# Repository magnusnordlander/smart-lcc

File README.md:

# Smart LCC

A smarter LCC for the Lelit Bianca V2, with Wi-Fi and stuff.

Based on the protocol dissection I'm doing in [magnusnordlander/lelit-bianca-protocol](https://github.com/magnusnordlander/lelit-bianca-protocol).

**This project is moving to [https://github.com/variegated-coffee](https://github.com/variegated-coffee). Don't manufacture this board, there's a new revision coming.**

## Status

Consider this project beta quality.

The revision B PCB works well. Manufacturing files are available in the `pcb/` directory. Unless you're *very* good at soldering fine pitch by hand, I suggest manufacturing with SMT assembly. I've used JLCPCB for my manufacturing runs, and the files have worked well there. I do have some spares of both the Rev A PCB (just the PCB) and the Rev B PCB (the difficult components already soldered, but does need a connector, buttons, a display and an Arduino). If you have experience of embedded programming, want to help with the project and you want one of the PCBs, reach out.

I am considering making a Rev C PCB that doesn't use an Arduino, but rather RP2040 and ESP32 chips directly. This would allow for a relocated display connector (similar to the original LCC) and a better antenna, which is useful since the board is located inside a metal enclosure. We'll have to see though.

Considering this plugs in to an expensive machine it bears to mention: Anything you do with this, you do at your own risk. Components have been fried already during the course of this project. Your machine uses both line voltage power, high pressured hot water, steam and other dangerous components. There is a risk of both damaging the machine, personal injury and property damage, the liability for which you assume yourself. This is not the stage to get on board with this project if you aren't willing to deal with those risks. 

### A note on Bianca versions

This project has only been tested on a Bianca V2. There are (at the time of writing) three versions of the Bianca, V1, V2, and V3. To my understanding it should work on a Bianca V1, but it's untested. As for the Bianca V3, it features upgraded hardware (a different solenoid valve with high/low flow signals), which this project doesn't support. Since I don't have access to a Bianca V3 (for reverse engineering or otherwise), support is currently not on the roadmap.

The LCC-relevant hardware differences between a V2 and a V3 Bianca (to my understanding) are the following:

* A new solenoid to control full/low flow from the pump (upgradable via the V3 upgrade kit)
* The power light now an LED and software controlled (not a part of the V3 upgrade kit)

Most notably, the Gicar box is the same, which is very interesting.

Like I said, I do not have access to a Bianca V3, so reverse engineering the protocol changes for the V3 would be difficult, and validation would be impossible. That being said, if someone were to reverse engineer the protocol changes, a new version of this firmware could be made that would be backwards-compatible with the Bianca V2. That is absolutely an interesting proposition.

## Project goals

Create a smart replacement for the "LCC" PID module used in the Lelit Bianca with open source hardware and software.

## Architecture

### Hardware
This project is using the Arduino RP2040 Connect, a dual core ARM Cortex-M0+ board with a Ublox Nina W102 module.

A custom PCB has been designed (see `pcb/`) that is designed to fit in the original LCC enclosure. A BOM for components is also available. Aside from the Arduino RP2040 Connect, the PCB has push buttons for + and -, a resistor divider for the 5V Control Board UART signal, and a flat flex connector for a SSD1309 based OLED. The PCB has been designed with surface mount components, but uses relatively large 1206 caps and resistors, which are somewhat simple to hand solder.

#### Possible future revision
I have been considering a new hardware revision, which instead of using an Arduino RP2040 Connect, uses just a plain RP2040, and a plain ESP32 (of some kind, though if I know myself, it'll probably be an ESP32-S3).

The main motivations are the following: 

* Allowing a better WiFi antenna (the Bianca is basically a faraday cage, so a better antenna would be beneficial)
* Allowing for separate programming ports on the board for the ESP32 and the RP2040
* Possibly attaching the RP2040 QSPI Flash to the ESP32 as well, for easier OTA updates
* Allowing for a cutout for the display ribbon cable, similar to the cutout on the original LCC board

There's also a couple of more errata like things I would add in a new revision:

* Use just a Zener instead of resistor divider to shift the 5V UART to 3V3

This being said, I haven't made up my mind about whether to do a future revision at all.

### Firmware (1.0.0, current)
The project is using arduino-cli, with earlephilhower/arduino-pico. Core 0 runs UI and external communications, and will communicate with core 1 through `pico_util/queue`. Core1 does not *store* it's parameters. Core0 reads them from LittleFS, and passes them to Core1 through regular message passing.

#### Usage
Hold the plus button while booting to trigger configuration mode. In configuration mode, a safe packet is continually sent to the control board, and a WiFi access point is created, with the SSID `LCC-XXXXXX`, where `XXXXXX` is the last 6 hex digits of the unit's MAC address. It is password protected, using the same password as the SSID, (i.e. `LCC-XXXXXX`). Therein you can configure your WiFi network and MQTT settings.

Hold the minus button while booting to trigger OTA mode. As in configuration mode, a safe packet is continually sent to the control board. It connects to the WiFi configured in configuration mode. Use ArduinoOTA to send new firmware. The controller doesn't automatically reboot after OTA, so after the OTA is complete and the display goes blank, manually cycle power.

#### RP2040 Core 0
* UI controller
* External communication

#### RP2040 Core 1
* System controller
  * Safety critical, uses the entire core for itself
  * Communicates with the Control Board
  * Performs a safety check, ensuring that temperatures in the boilers never exceed safe limits, and that both boilers are never running simultaneously.
  * Responsible for kicking the watchdog
    * Reboots if Core 0 isn't handling its messages (i.e. has crashed or is frozen)
  * Responsible for PID, keeping water in the boiler, running pumps etc.

#### Core communication protocol

##### Core1 to Core0

* One message type
  * Timestamp (absolute_time_t) 
  * Brew temperature
  * Brew set point
  * Brew PID settings
  * Brew PID parameters
  * Service temperature
  * Service set point
  * Service PID settings
  * Service PID parameters
  * Eco mode
  * System state
    * Idle
    * Heatup
    * Warm
    * Sleeping
    * Bailed
    * First run (fill all the boilers before heating them)
  * Bail reason
  * Brewing
  * Filling service boiler
  * Water low

##### Core0 to Core1

* Multiple message types
  * Set Brew Set Point (Non compensated)
  * Set Brew PID Parameters
  * Set Service Set Point
  * Set Service PID Parameters
  * Set Eco Mode (on/off)
  * Set Sleep mode (on/off)
  * Unbail
  * Trigger first run
* Payloads
  * Float 1
    * Brew set point
    * Service boiler set point
    * Kp
  * Float 2
    * Ki
  * Float 3
    * Kd
  * Bool
    * Eco mode
    * Sleep mode

### Firmware 1.1.0
In this firmware, Core0 and Core1 will swap functions.

### Firmware 2.0.0
In this firmware, a custom firmware for the Ublox Nina W102 will be developed to handle network communication.

### Reference material
(In no particular order)

* https://github.com/improv-wifi/sdk-cpp
* https://www.youtube.com/watch?v=fAEDHOUJCEo
* Random facts about the stock implementation:
  * Some implementation details are available in https://www.1st-line.com/wp-content/uploads/2018/12/Parameter-settings-technical-menu-Bianca-PL162T.pdf
    * Original parameters (not necessarily applicable since PID parameters are hightly implementation dependent):
      * Brew boiler
        * Kp: 0.8
        * Ki: 0.04
        * Kd: 12
        * On/off delta: 15°C
      * Service boiler
        * Kp: 20
        * Ki: 0
        * Kd: 20
        * On/off delta: 0
      * Brew boiler offset: 10°C
    * A "full" heatup cycle goes to 130°C first, then drops to set temperature
      * Triggered when the temperature on power on is less than 70°C
    * Service boiler is not PID controlled (even though it can be). Even if it *were*, having a Ki of 0, means it's a PD controller. It's a simple on/off controller.
  * Minimum on/off-time seems to be around 100-120 ms
  * When in eco mode, a warmup consists of running the coffee boiler full blast, holding the temperature around 130°C for 4 minutes, then dropping to the set point
  * When in regular mode, there is a kind of time slot system for which boiler is used. The time slots are 1 second wide.
  * Shot saving seems to be implemented by simply blocking new brews from starting when the tank is empty. There's no fanciness with allowing it to run for a certain amount of time or anything.
  * It takes about 3 seconds for the LCC to pick up on an empty water tank (presumably to debounce the signal)

## Licensing

The firmware is MIT licensed (excepting dependencies, which have their own, compatible licenses), and the hardware is CERN-OHL-P.

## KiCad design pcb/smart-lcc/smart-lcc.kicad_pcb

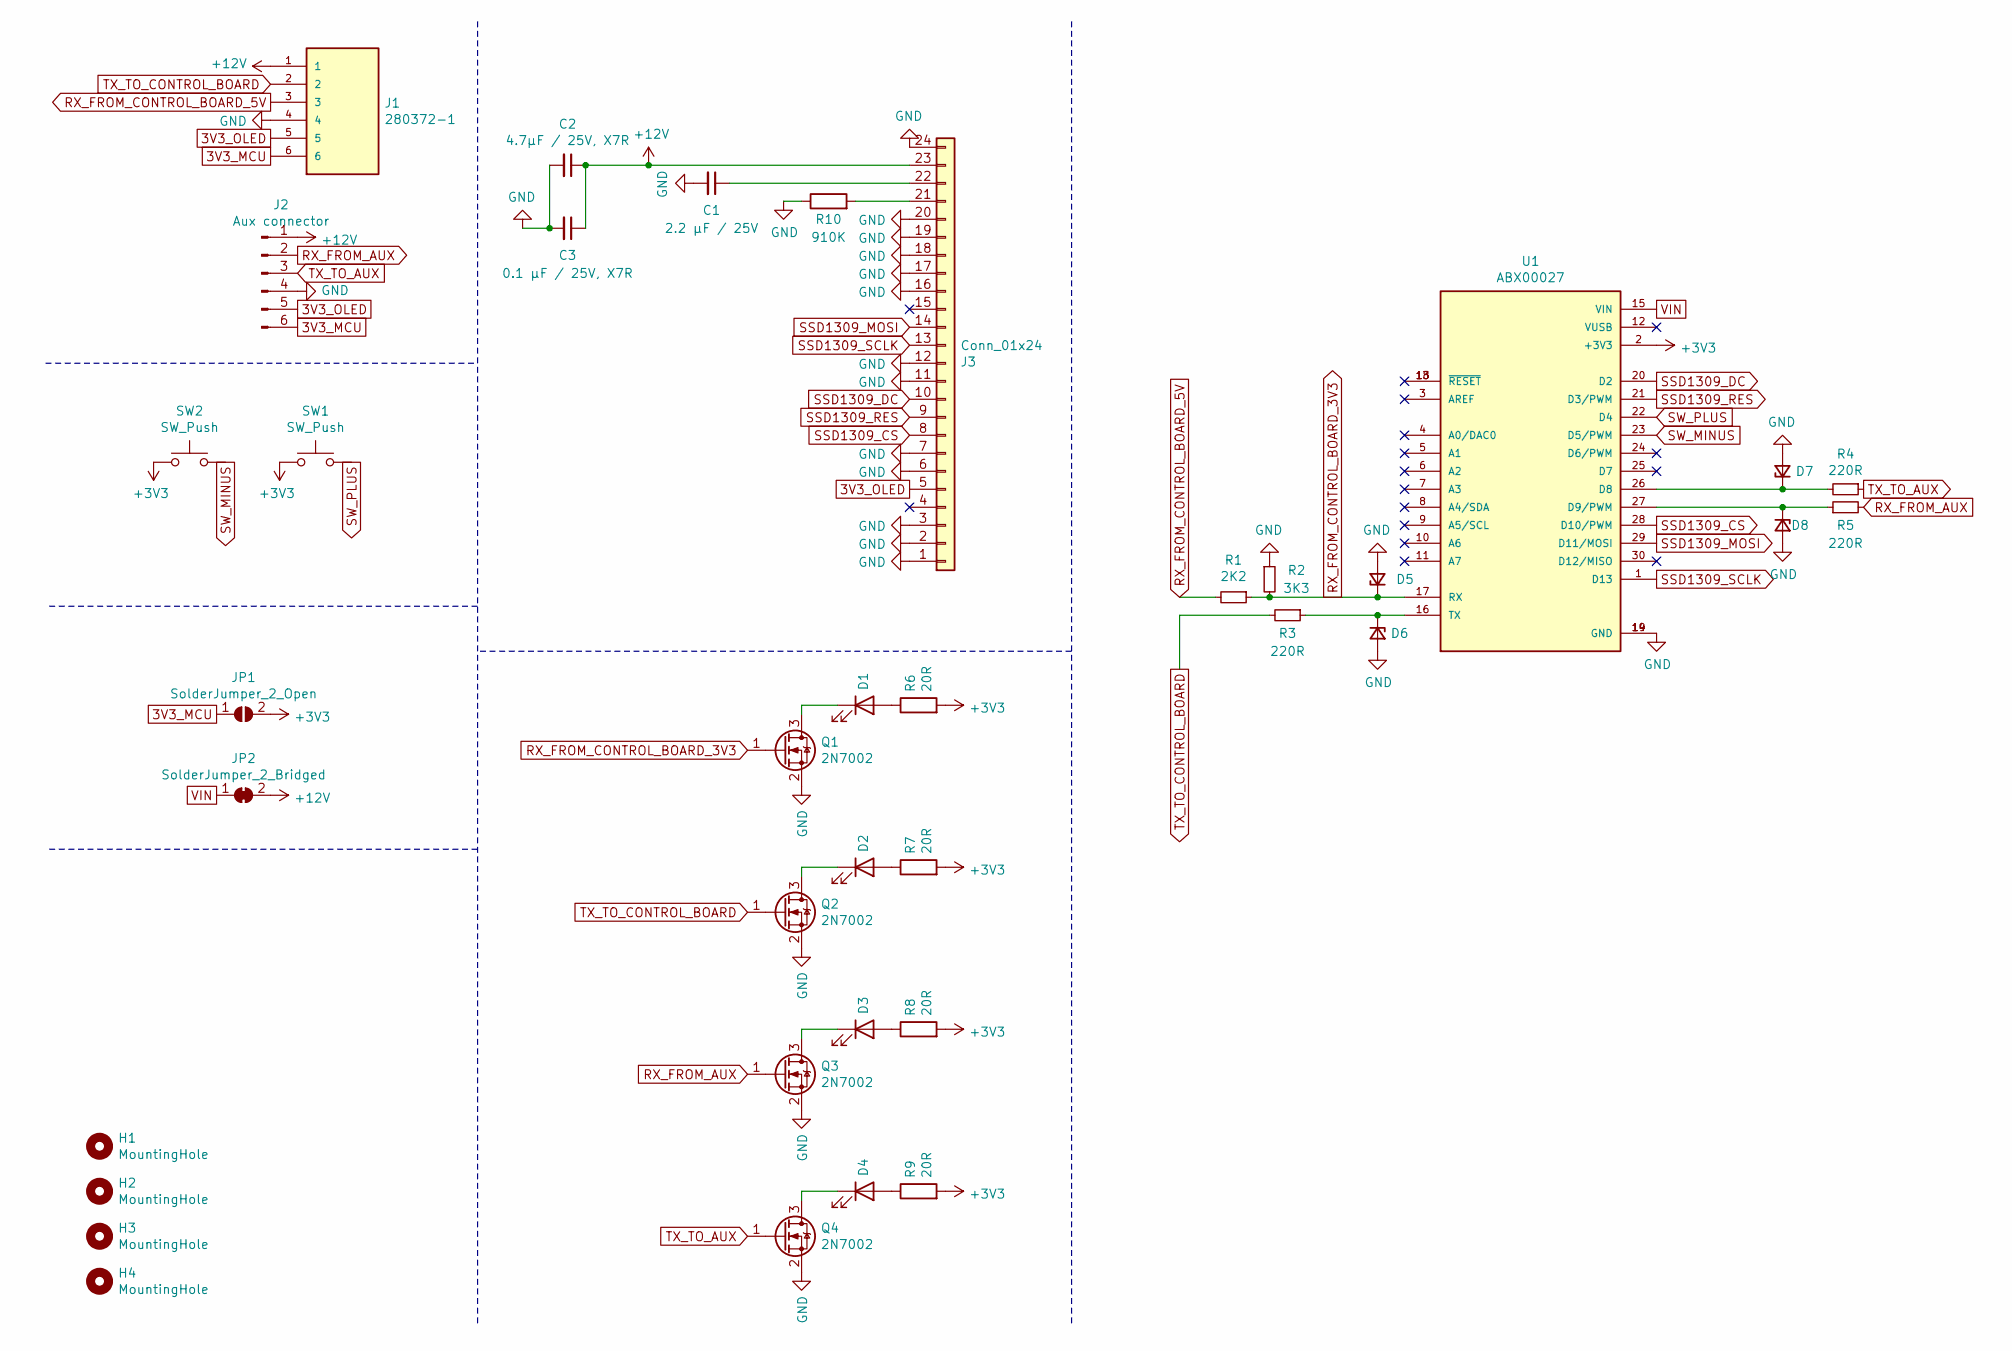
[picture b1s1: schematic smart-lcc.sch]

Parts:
C1: 2.2 µF / 25V; C_0805_2012Metric; JLCPCB Basic Y
C2: 4.7µF / 25V, X7R; C_1206_3216Metric; JLCPCB Basic Y
C3: 0.1 µF / 25V, X7R; C_0603_1608Metric; JLCPCB Basic Y
D1, D2, D3, D4: 19-217/BHC-ZL1M2RY/3T; LED_0603_1608Metric; JLCPCB Basic Y
D5, D6, D7, D8: D_Zener_Small; D_SOD-123; JLCPCB Basic N
H1, H2, H3, H4: MountingHole; MountingHole_2.7mm
J1: 280372-1; TE_280372-1
J2: Aux connector; PinHeader_1x06_P2.54mm_Vertical
J3: Conn_01x24; FH34SRJ24S05SH50; JLCPCB Basic N
JP1: SolderJumper_2_Open; SolderJumper-2_P1.3mm_Open_RoundedPad1.0x1.5mm
JP2: SolderJumper_2_Bridged; SolderJumper-2_P1.3mm_Bridged_RoundedPad1.0x1.5mm
Q1, Q2, Q3, Q4: 2N7002; SOT-23; JLCPCB Basic Y
R1: 2K2; R_0402_1005Metric; JLCPCB Basic Y
R2: 3K3; R_0402_1005Metric; JLCPCB Basic Y
R3, R4, R5: 220R; R_0402_1005Metric; JLCPCB Basic Y
R6, R7, R8, R9: 20R; R_0603_1608Metric; JLCPCB Basic Y
R10: 910K; R_0603_1608Metric; JLCPCB Basic N
SW1, SW2: SW_Push; ADTSMW65
U1: ABX00027; MODULE_ABX00027

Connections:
3V3_MCU: J1.6, J2.6, JP1.1 (A)
3V3_OLED: J1.5, J2.5, J3.5
+3V3: JP1.2 (B), R6.2, R7.2, R8.2, R9.2, SW1.1, SW2.1, U1.2 (+3V3)
+12V: C2.1, C3.1, J1.1, J2.1, J3.23, JP2.2 (B)
GND: C1.2, C2.2, C3.2, D5.2 (A), D6.2 (A), D7.2 (A), D8.2 (A), J1.4, J2.4, J3.1, J3.2, J3.3, J3.6, J3.7, J3.11, J3.12, J3.16, J3.17, J3.18, J3.19, J3.20, J3.24, Q1.2 (S), Q2.2 (S), Q3.2 (S), Q4.2 (S), R2.1, R10.1, U1.14 (GND), U1.19 (GND)
unnamed: C1.1, J3.22
unnamed: D1.1 (K), Q1.3 (D)
unnamed: D1.2 (A), R6.1
unnamed: D2.1 (K), Q2.3 (D)
unnamed: D2.2 (A), R7.1
unnamed: D3.1 (K), Q3.3 (D)
unnamed: D3.2 (A), R8.1
unnamed: D4.1 (K), Q4.3 (D)
unnamed: D4.2 (A), R9.1
unnamed: D6.1 (K), R3.1, U1.16 (TX)
unnamed: D7.1 (K), R4.2, U1.26 (D8)
unnamed: D8.1 (K), R5.1, U1.27 (D9/PWM)
unnamed: J3.21, R10.2
unnamed: U1.13 (~RESET), U1.18 (~RESET)
RX_FROM_AUX: J2.2, Q3.1 (G), R5.2
RX_FROM_CONTROL_BOARD_3V3: D5.1 (K), Q1.1 (G), R1.1, R2.2, U1.17 (RX)
RX_FROM_CONTROL_BOARD_5V: J1.3, R1.2
SSD1309_CS: J3.8, U1.28 (D10/PWM)
SSD1309_DC: J3.10, U1.20 (D2)
SSD1309_MOSI: J3.14, U1.29 (D11/MOSI)
SSD1309_RES: J3.9, U1.21 (D3/PWM)
SSD1309_SCLK: J3.13, U1.1 (D13)
SW_MINUS: SW2.2, U1.23 (D5/PWM)
SW_PLUS: SW1.2, U1.22 (D4)
TX_TO_AUX: J2.3, Q4.1 (G), R4.1
TX_TO_CONTROL_BOARD: J1.2, Q2.1 (G), R3.2
VIN: JP2.1 (A), U1.15 (VIN)

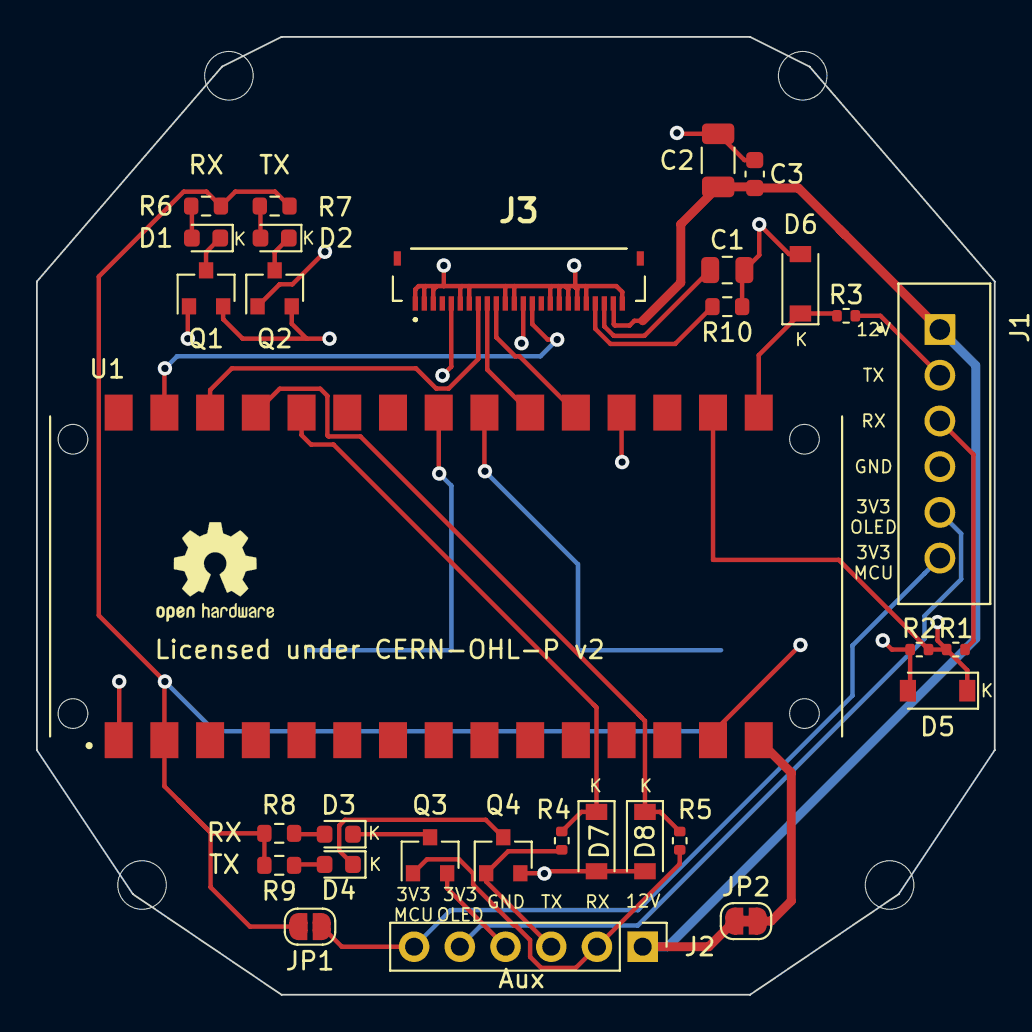
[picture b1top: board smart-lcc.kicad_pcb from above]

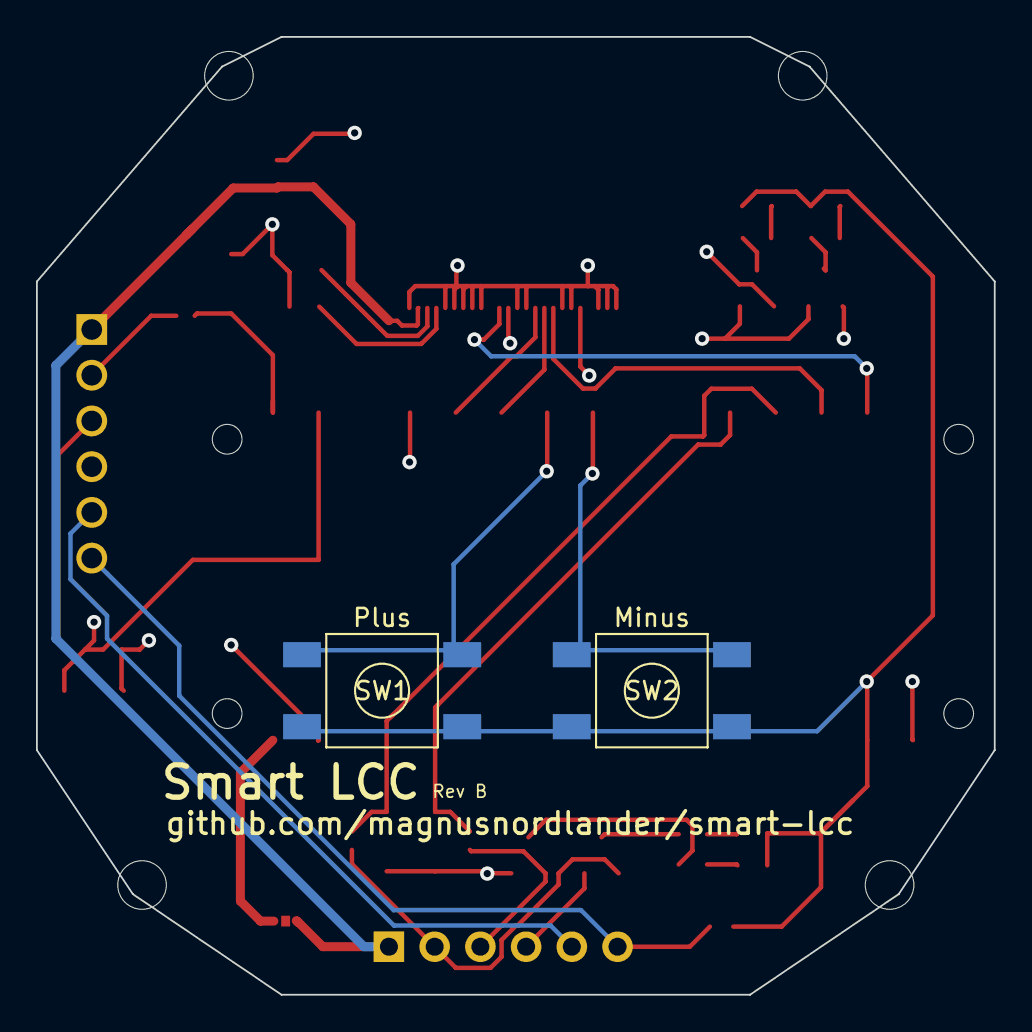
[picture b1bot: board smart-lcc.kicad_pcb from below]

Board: 4 copper layers, 53.2 x 53.2 mm, 37 parts (2 on the bottom side), 32 nets.

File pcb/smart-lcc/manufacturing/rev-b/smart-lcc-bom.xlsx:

Designator | Comment | Footprint | LCSC | Qty
C1 | 2.2 µF / 25V | Capacitor_SMD:C_0805_2012Metric | C49217 | 1
C2 | 4.7µF / 25V, X7R | Capacitor_SMD:C_1206_3216Metric | C29823 | 1
C3 | 0.1 µF / 25V, X7R | Capacitor_SMD:C_0603_1608Metric | C14663 | 1
D1,D2,D3,D4 | 19-217/BHC-ZL1M2RY/3T | LED_SMD:LED_0603_1608Metric | C72041 | 4
D5,D6,D7,D8 | D_Zener_Small | Diode_SMD:D_SOD-123 | C707129 | 4
J3 | Conn_01x24 | FH34SRJ-24S-0.5SH_50:FH34SRJ24S05SH50 | C324726 | 1
Q1,Q2,Q3,Q4 | 2N7002 | Package_TO_SOT_SMD:SOT-23 | C8545 | 4
R1 | 2K2 | Resistor_SMD:R_0402_1005Metric | C25879 | 1
R2 | 3K3 | Resistor_SMD:R_0402_1005Metric | C25890 | 1
R3,R4,R5 | 220R | Resistor_SMD:R_0402_1005Metric | C25091 | 3
R6,R7,R8,R9 | 20R | Resistor_SMD:R_0603_1608Metric | C22950 | 4
R10 | 910K | Resistor_SMD:R_0603_1608Metric | C141274 | 1

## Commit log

2021-03-14 Initial import
2021-03-14 Added Readme
2021-03-16 Changed algorithm for calculating temperatures
2021-06-26 Added PCB outline
2021-06-27 Work on PCB
2021-06-27 Bug fixes
2021-07-01 Getting ready to manufacture PCB
2021-07-01 Added Mk 1 manufacturing data
2021-07-02 Emulated rig tweaks
2021-07-02 Switched to Arduino/Mbed OS
2021-07-26 Create LICENSE
2021-07-26 Moved firmware license to the proper directory
2021-07-30 Started work on a rev b board
2021-07-31 Rev B as sent to manufacturing
2021-07-31 Notes on revision B
2021-08-08 Store settings in Mbed Key Value store
2021-08-18 Initial work on running the system controller on Core 1
2021-08-19 Removed rtos from more things
2021-08-20 Added enums
2021-08-20 Broken commit
2021-08-22 Added PID Feed forward
2021-08-23 Fix for crashes probably
2021-08-23 Remove ALL the printf:ed floats
2021-08-23 Revised validation
2021-08-26 Inverse linear feed forward factor
2021-08-27 Changed feed-forward parameters and force hysteresis when in heatup
2021-09-29 Changed Service boiler to always use a hysteresis controller
2021-10-08 Revert validation branch merge. I need to take a closer look at this.
    This reverts commit 4b7253f6960364933aa8ee0087ce2a289db623cf.
2022-01-07 WIP on MQTT autodiscovery
2022-01-08 Added MQTT Autoconfigure
2022-01-08 Save sleep state to flash
2022-01-08 Fixed saving sleep mode
2022-01-08 Fixed validation
2022-01-08 Validation fixes
2022-01-08 More fixes
2022-01-31 WIP: Switching to earlephilhower/arduino-pico and an Arduino CLI based toolchain
2022-02-11 Final changes for toolchain switch
2022-02-11 Arduino toolchain (#8)
    Switching to earlephilhower/arduino-pico and an Arduino CLI based toolchain
2022-02-11 Nicer UI
2022-02-12 Fixes, exiting sleep mode, and adding last brew time to MQTT
2022-02-13 Show the correct IP address on the OTA mode screen
2022-02-13 Button controls for sleep mode and brew temperature
2022-02-17 Auto sleep (#17)
    Added auto-sleep with a configurable time, and updated autodiscovery topics to be retained.
2022-02-18 Makefile fix
2022-02-18 Expose planned auto sleep through MQTT
2022-02-18 Implement shot saving (Fix #15)
2022-02-18 Copy all the uploaded uf2:s to a special directory when OTA updating prod
2022-02-18 Rename Network mode to System mode
2022-02-18 Swapped places between core 0 and 1
2022-02-22 Fixed Wifi disconnect errors
2022-12-13 Add Gitter badge
2022-12-13 Add Gitter badge (#18)
2022-12-22 Add RP2040 temperature to MQTT data
2023-01-26 Added number of bails and uptimes for ESP32 and RP2040.

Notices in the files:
pcb/smart-lcc/smart-lcc.kicad_pcb:
Licensed under CERN-OHL-P v2
